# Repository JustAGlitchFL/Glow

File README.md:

# Glow
Modular interconnected lighting system for videography

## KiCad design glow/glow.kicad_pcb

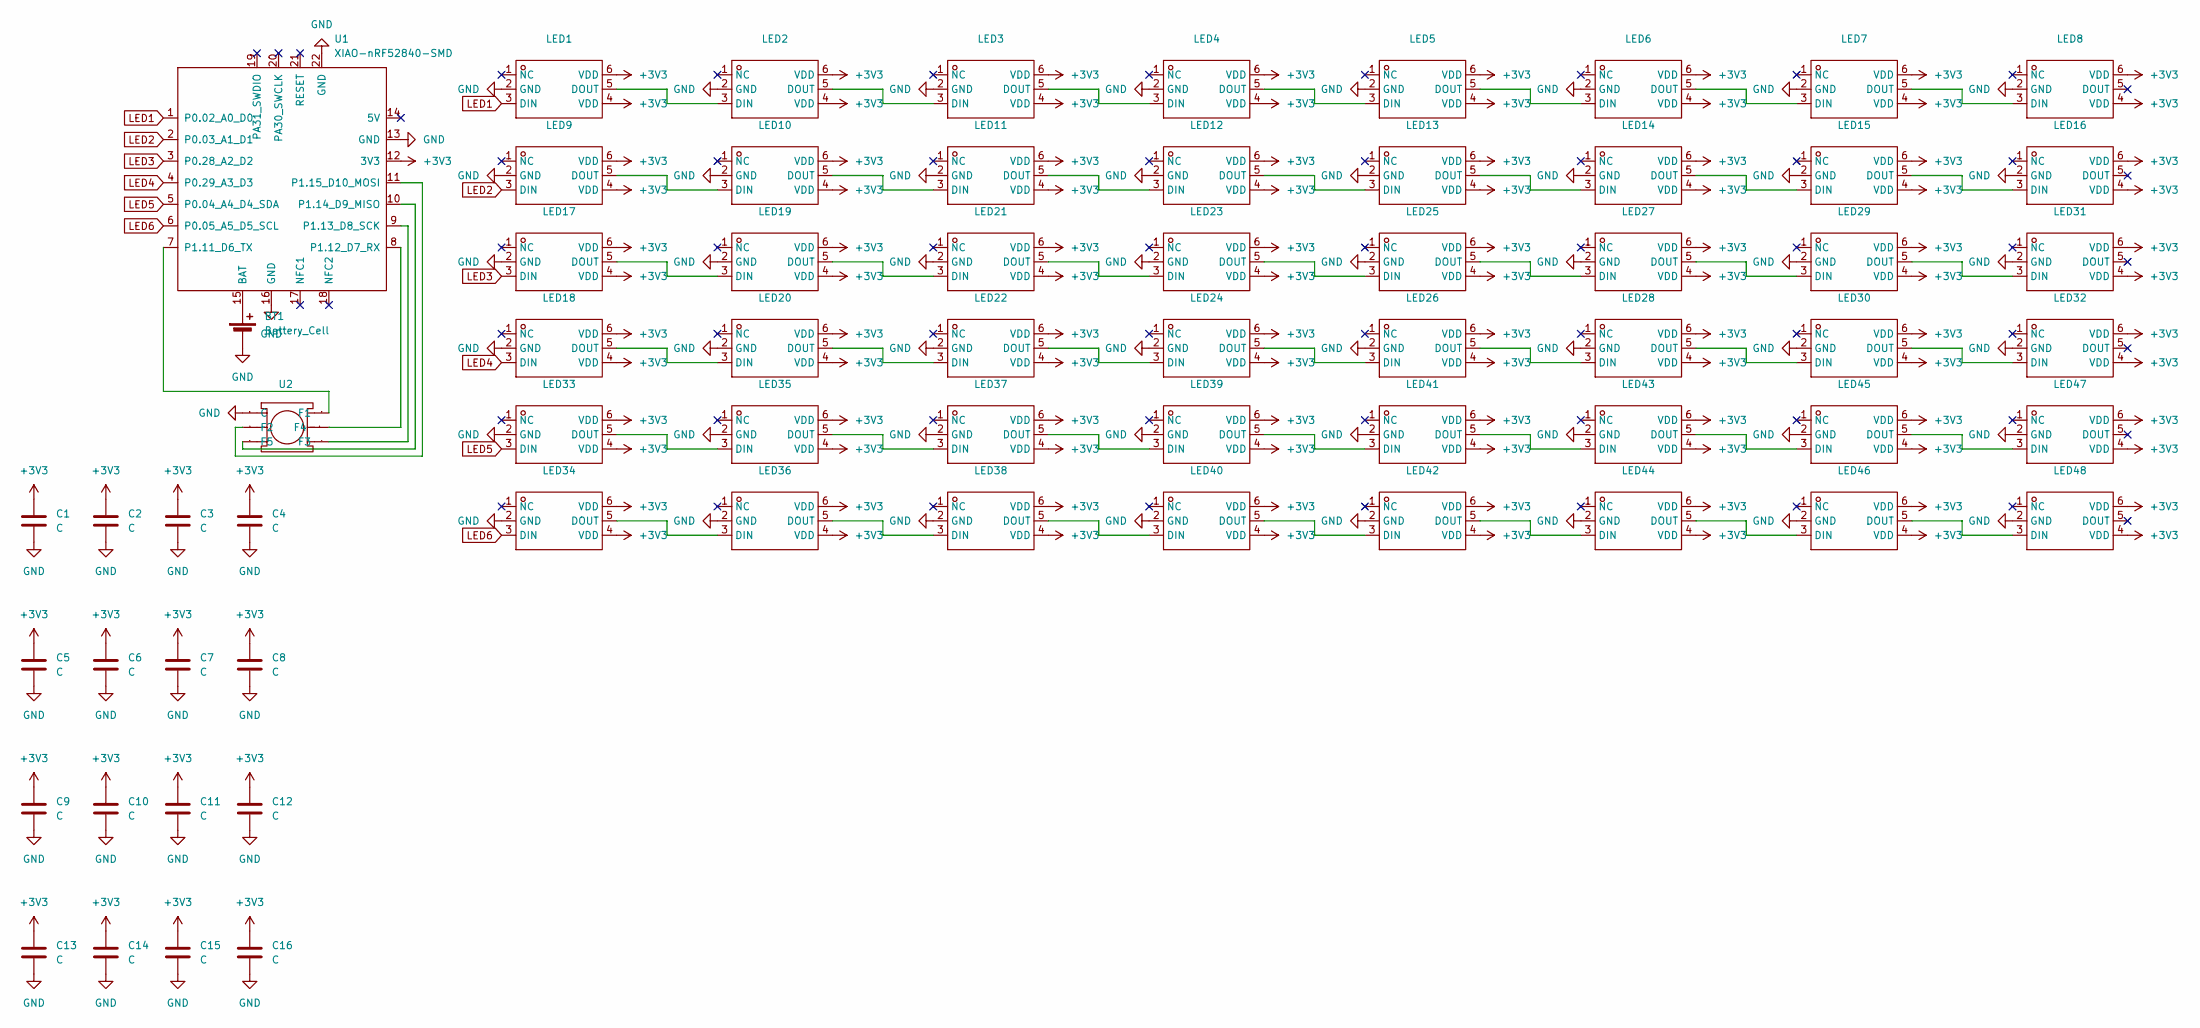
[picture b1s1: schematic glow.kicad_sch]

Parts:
BT1: Battery_Cell; PinHeader_1x02_P1.00mm_Vertical
C1, C2, C3, C4, C5, C6, C7, C8, C9, C10, C11, C12, C13, C14, C15, C16: C; C_0805_2012Metric_Pad1.18x1.45mm_HandSolder
LED1, LED2, LED3, LED4, LED5, LED6, LED7, LED8, LED9, LED10, LED11, LED12, LED13, LED14, LED15, LED16, LED17, LED18, LED19, LED20, LED21, LED22, LED23, LED24, LED25, LED26, LED27, LED28, LED29, LED30, LED31, LED32, LED33, LED34, LED35, LED36, LED37, LED38, LED39, LED40, LED41, LED42, LED43, LED44, LED45, LED46, LED47, LED48: LED-ARRAY-SMD_6P-L3.7-W3.5-TL_SK6812MINIRGBW-XW-P6-A-000; Manufacturer Part SK6812MINIRGBW-NW-P6
U1: XIAO-nRF52840-SMD
U2: SW-SMD_WS-1001-ACW09026; Manufacturer Part WS-1001-ACW09026

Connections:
+3V3: C1.1, C2.1, C3.1, C4.1, C5.1, C6.1, C7.1, C8.1, C9.1, C10.1, C11.1, C12.1, C13.1, C14.1, C15.1, C16.1, LED1.4 (VDD), LED1.6 (VDD), LED2.4 (VDD), LED2.6 (VDD), LED3.4 (VDD), LED3.6 (VDD), LED4.4 (VDD), LED4.6 (VDD), LED5.4 (VDD), LED5.6 (VDD), LED6.4 (VDD), LED6.6 (VDD), LED7.4 (VDD), LED7.6 (VDD), LED8.4 (VDD), LED8.6 (VDD), LED9.4 (VDD), LED9.6 (VDD), LED10.4 (VDD), LED10.6 (VDD), LED11.4 (VDD), LED11.6 (VDD), LED12.4 (VDD), LED12.6 (VDD), LED13.4 (VDD), LED13.6 (VDD), LED14.4 (VDD), LED14.6 (VDD), LED15.4 (VDD), LED15.6 (VDD), LED16.4 (VDD), LED16.6 (VDD), LED17.4 (VDD), LED17.6 (VDD), LED18.4 (VDD), LED18.6 (VDD), LED19.4 (VDD), LED19.6 (VDD), LED20.4 (VDD), LED20.6 (VDD), LED21.4 (VDD), LED21.6 (VDD), LED22.4 (VDD), LED22.6 (VDD), LED23.4 (VDD), LED23.6 (VDD), LED24.4 (VDD), LED24.6 (VDD), LED25.4 (VDD), LED25.6 (VDD), LED26.4 (VDD), LED26.6 (VDD), LED27.4 (VDD), LED27.6 (VDD), LED28.4 (VDD), LED28.6 (VDD), LED29.4 (VDD), LED29.6 (VDD), LED30.4 (VDD), LED30.6 (VDD), LED31.4 (VDD), LED31.6 (VDD), LED32.4 (VDD), LED32.6 (VDD), LED33.4 (VDD), LED33.6 (VDD), LED34.4 (VDD), LED34.6 (VDD), LED35.4 (VDD), LED35.6 (VDD), LED36.4 (VDD), LED36.6 (VDD), LED37.4 (VDD), LED37.6 (VDD), LED38.4 (VDD), LED38.6 (VDD), LED39.4 (VDD), LED39.6 (VDD), LED40.4 (VDD), LED40.6 (VDD), LED41.4 (VDD), LED41.6 (VDD), LED42.4 (VDD), LED42.6 (VDD), LED43.4 (VDD), LED43.6 (VDD), LED44.4 (VDD), LED44.6 (VDD), LED45.4 (VDD), LED45.6 (VDD), LED46.4 (VDD), LED46.6 (VDD), LED47.4 (VDD), LED47.6 (VDD), LED48.4 (VDD), LED48.6 (VDD), U1.12 (3V3)
GND: BT1.2 (-), C1.2, C2.2, C3.2, C4.2, C5.2, C6.2, C7.2, C8.2, C9.2, C10.2, C11.2, C12.2, C13.2, C14.2, C15.2, C16.2, LED1.2 (GND), LED2.2 (GND), LED3.2 (GND), LED4.2 (GND), LED5.2 (GND), LED6.2 (GND), LED7.2 (GND), LED8.2 (GND), LED9.2 (GND), LED10.2 (GND), LED11.2 (GND), LED12.2 (GND), LED13.2 (GND), LED14.2 (GND), LED15.2 (GND), LED16.2 (GND), LED17.2 (GND), LED18.2 (GND), LED19.2 (GND), LED20.2 (GND), LED21.2 (GND), LED22.2 (GND), LED23.2 (GND), LED24.2 (GND), LED25.2 (GND), LED26.2 (GND), LED27.2 (GND), LED28.2 (GND), LED29.2 (GND), LED30.2 (GND), LED31.2 (GND), LED32.2 (GND), LED33.2 (GND), LED34.2 (GND), LED35.2 (GND), LED36.2 (GND), LED37.2 (GND), LED38.2 (GND), LED39.2 (GND), LED40.2 (GND), LED41.2 (GND), LED42.2 (GND), LED43.2 (GND), LED44.2 (GND), LED45.2 (GND), LED46.2 (GND), LED47.2 (GND), LED48.2 (GND), U1.13 (GND), U1.16 (GND), U1.22 (GND), U2.1 (C)
LED1: LED1.3 (DIN), U1.1 (P0.02_A0_D0)
LED2: LED9.3 (DIN), U1.2 (P0.03_A1_D1)
LED3: LED17.3 (DIN), U1.3 (P0.28_A2_D2)
LED4: LED18.3 (DIN), U1.4 (P0.29_A3_D3)
LED5: LED33.3 (DIN), U1.5 (P0.04_A4_D4_SDA)
LED6: LED34.3 (DIN), U1.6 (P0.05_A5_D5_SCL)
unnamed: BT1.1 (+), U1.15 (BAT)
unnamed: LED1.5 (DOUT), LED2.3 (DIN)
unnamed: LED2.5 (DOUT), LED3.3 (DIN)
unnamed: LED3.5 (DOUT), LED4.3 (DIN)
unnamed: LED4.5 (DOUT), LED5.3 (DIN)
unnamed: LED5.5 (DOUT), LED6.3 (DIN)
unnamed: LED6.5 (DOUT), LED7.3 (DIN)
unnamed: LED7.5 (DOUT), LED8.3 (DIN)
unnamed: LED9.5 (DOUT), LED10.3 (DIN)
unnamed: LED10.5 (DOUT), LED11.3 (DIN)
unnamed: LED11.5 (DOUT), LED12.3 (DIN)
unnamed: LED12.5 (DOUT), LED13.3 (DIN)
unnamed: LED13.5 (DOUT), LED14.3 (DIN)
unnamed: LED14.5 (DOUT), LED15.3 (DIN)
unnamed: LED15.5 (DOUT), LED16.3 (DIN)
unnamed: LED17.5 (DOUT), LED19.3 (DIN)
unnamed: LED18.5 (DOUT), LED20.3 (DIN)
unnamed: LED19.5 (DOUT), LED21.3 (DIN)
unnamed: LED20.5 (DOUT), LED22.3 (DIN)
unnamed: LED21.5 (DOUT), LED23.3 (DIN)
unnamed: LED22.5 (DOUT), LED24.3 (DIN)
unnamed: LED23.5 (DOUT), LED25.3 (DIN)
unnamed: LED24.5 (DOUT), LED26.3 (DIN)
unnamed: LED25.5 (DOUT), LED27.3 (DIN)
unnamed: LED26.5 (DOUT), LED28.3 (DIN)
unnamed: LED27.5 (DOUT), LED29.3 (DIN)
unnamed: LED28.5 (DOUT), LED30.3 (DIN)
unnamed: LED29.5 (DOUT), LED31.3 (DIN)
unnamed: LED30.5 (DOUT), LED32.3 (DIN)
unnamed: LED33.5 (DOUT), LED35.3 (DIN)
unnamed: LED34.5 (DOUT), LED36.3 (DIN)
unnamed: LED35.5 (DOUT), LED37.3 (DIN)
unnamed: LED36.5 (DOUT), LED38.3 (DIN)
unnamed: LED37.5 (DOUT), LED39.3 (DIN)
unnamed: LED38.5 (DOUT), LED40.3 (DIN)
unnamed: LED39.5 (DOUT), LED41.3 (DIN)
unnamed: LED40.5 (DOUT), LED42.3 (DIN)
unnamed: LED41.5 (DOUT), LED43.3 (DIN)
unnamed: LED42.5 (DOUT), LED44.3 (DIN)
unnamed: LED43.5 (DOUT), LED45.3 (DIN)
unnamed: LED44.5 (DOUT), LED46.3 (DIN)
unnamed: LED45.5 (DOUT), LED47.3 (DIN)
unnamed: LED46.5 (DOUT), LED48.3 (DIN)
unnamed: U1.7 (P1.11_D6_TX), U2.4 (F1)
unnamed: U1.8 (P1.12_D7_RX), U2.5 (F4)
unnamed: U1.9 (P1.13_D8_SCK), U2.6 (F3)
unnamed: U1.10 (P1.14_D9_MISO), U2.3 (F5)
unnamed: U1.11 (P1.15_D10_MOSI), U2.2 (F2)

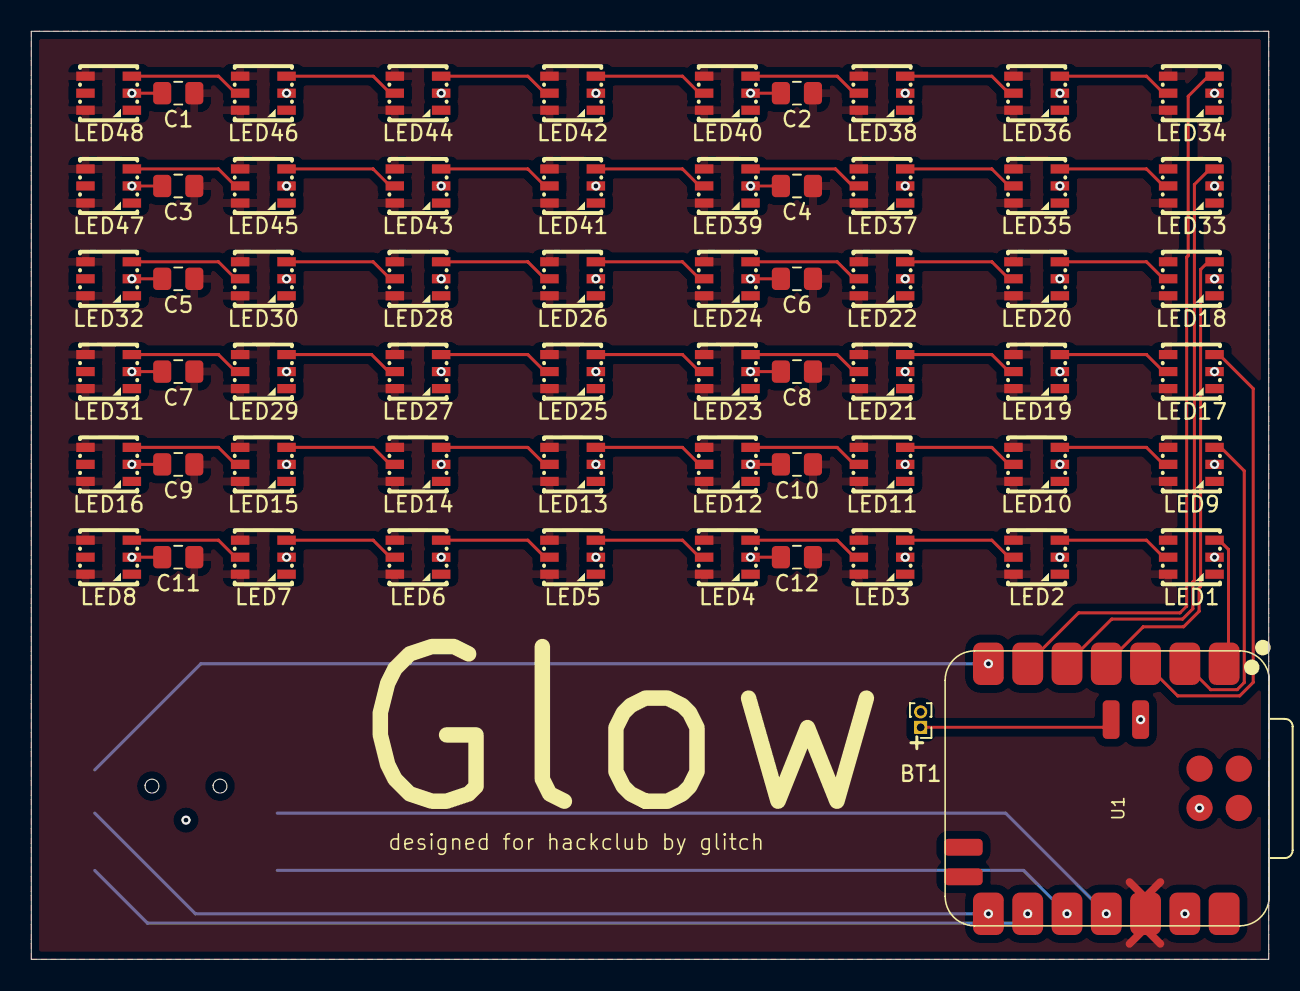
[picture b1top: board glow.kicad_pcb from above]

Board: 2 copper layers, 80.0 x 60.0 mm, 63 parts (1 on the bottom side), 56 nets.

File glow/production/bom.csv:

Designator,Footprint,Quantity,Value,LCSC Part #
BT1,PinHeader_1x02_P1.00mm_Vertical,1,Battery_Cell,
"C1, C10, C11, C12, C2, C3, C4, C5, C6, C7, C8, C9",0805,12,C,
"LED1, LED10, LED11, LED12, LED13, LED14, LED15, LED16, LED17, LED18, LED19, LED2, LED20, LED21, LED22, LED23, LED24, LED25, LED26, LED27, LED28, LED29, LED3, LED30, LED31, LED32, LED33, LED34, LED35, LED36, LED37, LED38, LED39, LED4, LED40, LED41, LED42, LED43, LED44, LED45, LED46, LED47, LED48, LED5, LED6, LED7, LED8, LED9",LED-ARRAY-SMD_6P-L3.7-W3.5-TL_SK6812MINIRGBW-XW-P6-A-000,48,~,
U1,XIAO-nRF52840-SMD,1,XIAO-nRF52840-SMD,
U2,SW-SMD_WS-1001-ACW09026,1,~,

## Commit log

2025-06-19 sync
2025-07-08 stuff
2025-07-22 dfgh
